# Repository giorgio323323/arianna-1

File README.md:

# Arianna
Arianna: il robot biblitecario.

il progetto è stato portato in: https://github.com/giorgio323323/ARI_V3

## Introduzione

Da [Arianna by CSBNO](http://webopac.csbno.net/library/Canegrate/makers-lab/arianna/) :
> Arrivo in biblioteca e chiedo “Robinia Blues” di Valter Binaghi, il bibliotecario consulta il computer e mi informa che c’è e lo posso trovare tra gli autori italiani. Un attimo di imbarazzo, non frequento questo luogo abbastanza da conoscere la disposizione degli scaffali, faccio per domandare ma il mio interlocutore mi anticipa dicendomi di seguire Arianna. Arianna? Un sibilo mi fa voltare, vedo una macchinina che parte lungo il corridoio, porta la scritta Arianna. Al mio sguardo interrogativo il mio interlocutore mi fa cenno di andare, segua Arianna mi dice. Tutto dura pochi secondi nei quali valuto anche la possibilità di essere vittima di “Scherzi a parte”, Arianna si ferma, si gira un poco e con un altro fruscio un puntatore luminoso si muove, si accende e quando decido di guardare dove Arianna sembra “indicare” vedo una luce sui libri e li vicino il mio “Robina Blues”. Lo prendo, lo sfoglio e me ne vado un poco stupito, saluto il bibliotecario e nel frattempo risento il sibilo. Vedo Arianna che torna da dove era venuta, la vedo accoccolarsi in una piccola casetta e io lascio la biblioteca pronto a rileggere il libro di un bravo insegnante che ha attraversato i nostri luoghi.

## Obiettivo 
La costruzione di un robot ***autonomo*** ed ***indipendente*** con lo scopo di accompagnare una persona al libro richiesto. La navigazione avviene in un ambiente dinamico dove anche i singli scaffali possono cambiare di posizione.

## Roadmap

- [x] Start
- [x] Primi prototipi (Ambros,Arianna,4rianna,..)
- Struttura
    - [ ] Arianna
    - [ ] Ambros
    - [ ] 4rianna
    - [ ] ..
- Movimento
    - [ ] Motori DC
    - [x] Stepper
    - [ ] Altro
- Altro
- [ ] Interazione biblio DB

## Contatti
[STUFFcube](https://stuffcube.wordpress.com/)

## License

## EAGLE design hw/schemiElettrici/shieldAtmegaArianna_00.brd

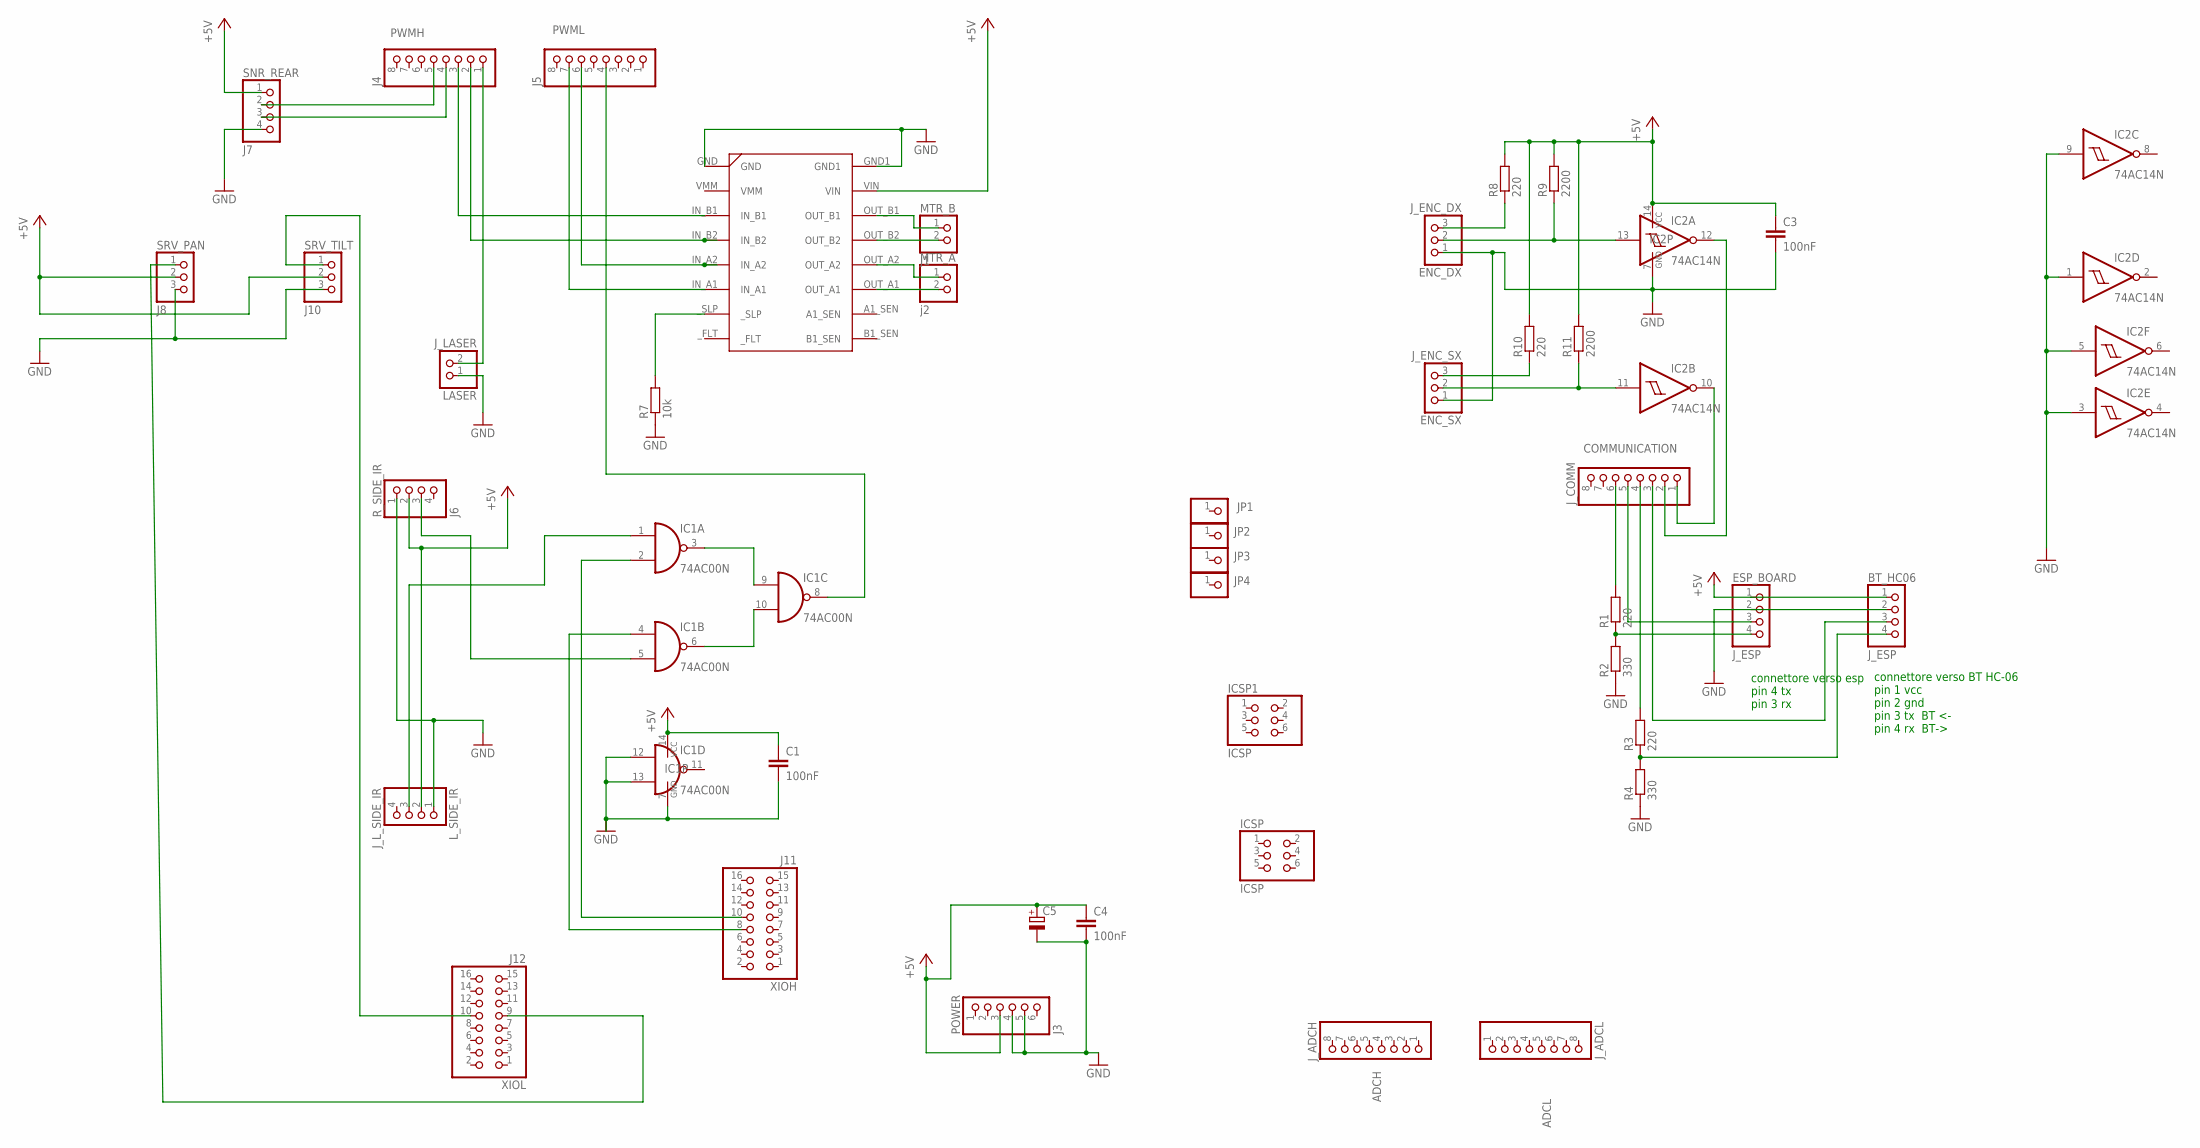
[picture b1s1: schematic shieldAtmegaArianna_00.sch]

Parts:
ADCH: J_ADCH; 1X08
ADCL: J_ADCL; 1X08
BT_HC06: J_ESP; 1X04
C1, C3, C4: 100nF; C050-025X075
C5: CPOL-EUE5-8.5; E5-8,5
COMMUNICATION: J_COMM; 1X08
ENC_DX: J_ENC_DX; 1X03
ENC_SX: J_ENC_SX; 1X03
ESP_BOARD: J_ESP; 1X04
IC1: 74AC00N; DIL14
IC2: 74AC14N; DIL14
ICSP, ICSP1: ICSP; 2X03
JP1, JP2, JP3, JP4: PINHD-1X1; 1X01
LASER: J_LASER; 1X02
L_SIDE_IR: J_L_SIDE_IR; 1X04
MTR_A: j2; 1X02
MTR_B: J1; 1X02
POWER: J3; 1X06
PWMH: J4; 1X08
PWML: J5; 1X08
R1, R3, R8, R10: 220; 0207/10
R2, R4: 330; 0207/10
R7: 10k; 0207/10
R9, R11: 2200; 0207/10
R_SIDE_IR: J6; 1X04
SNR_REAR: J7; 1X04
SRV_PAN: J8; 1X03
SRV_TILT: J10; 1X03
U$1: DRV8803; 8X5CARRIER
XIOH: J11; 2X08
XIOL: J12; 2X08

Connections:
+5V: BT_HC06.1, C1.1, C3.1, C4.1, C5.+, ESP_BOARD.1, IC1.14 (VCC), IC2.14 (VCC), L_SIDE_IR.2, POWER.3, R8.2, R9.2, R10.2, R11.2, R_SIDE_IR.2, SNR_REAR.1, SRV_PAN.2, SRV_TILT.2, U$1.VIN
ECHO: PWMH.4, SNR_REAR.3
GND: BT_HC06.2, C1.2, C3.2, C4.2, C5.-, ENC_DX.1, ENC_SX.1, ESP_BOARD.2, IC1.7 (GND), IC1.12 (I0), IC1.13 (I1), IC2.1 (I), IC2.3 (I), IC2.5 (I), IC2.7 (GND), IC2.9 (I), LASER.1, L_SIDE_IR.1, POWER.4, POWER.5, R2.1, R4.1, R7.1, R_SIDE_IR.1, SNR_REAR.4, SRV_PAN.3, SRV_TILT.3, U$1.GND, U$1.GND1
unnamed: MTR_B.1, U$1.OUT_B1
unnamed: MTR_B.2, U$1.OUT_B2
unnamed: MTR_A.1, U$1.OUT_A2
unnamed: SRV_TILT.1, XIOL.10
unnamed: SRV_PAN.1, XIOL.9
unnamed: MTR_A.2, U$1.OUT_A1
unnamed: PWML.7, U$1.IN_A1
unnamed: PWML.6, U$1.IN_A2
unnamed: PWMH.2, U$1.IN_B2
unnamed: PWMH.3, U$1.IN_B1
unnamed: ESP_BOARD.4, R1.1, R2.2
unnamed: BT_HC06.4, R3.1, R4.2
unnamed: COMMUNICATION.6, R1.2
unnamed: COMMUNICATION.4, R3.2
unnamed: COMMUNICATION.5, ESP_BOARD.3
unnamed: BT_HC06.3, COMMUNICATION.3
unnamed: IC1.3 (O), IC1.9 (I0)
unnamed: IC1.6 (O), IC1.10 (I1)
unnamed: LASER.2, PWMH.1
unnamed: IC1.2 (I1), XIOH.10
unnamed: IC1.5 (I1), R_SIDE_IR.3
unnamed: IC1.8 (O), PWML.4
unnamed: IC1.1 (I0), L_SIDE_IR.3
unnamed: IC1.4 (I0), XIOH.8
unnamed: R7.2, U$1._SLP
unnamed: ENC_DX.3, R8.1
unnamed: ENC_DX.2, IC2.13 (I), R9.1
unnamed: ENC_SX.3, R10.1
unnamed: PWMH.5, SNR_REAR.2
unnamed: ENC_SX.2, IC2.11 (I), R11.1
unnamed: COMMUNICATION.2, IC2.12 (O)
unnamed: COMMUNICATION.1, IC2.10 (O)

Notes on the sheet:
connettore verso esp pin 4 tx pin 3 rx
connettore verso BT HC-06 pin 1 vcc pin 2 gnd pin 3 tx BT <- pin 4 rx BT->

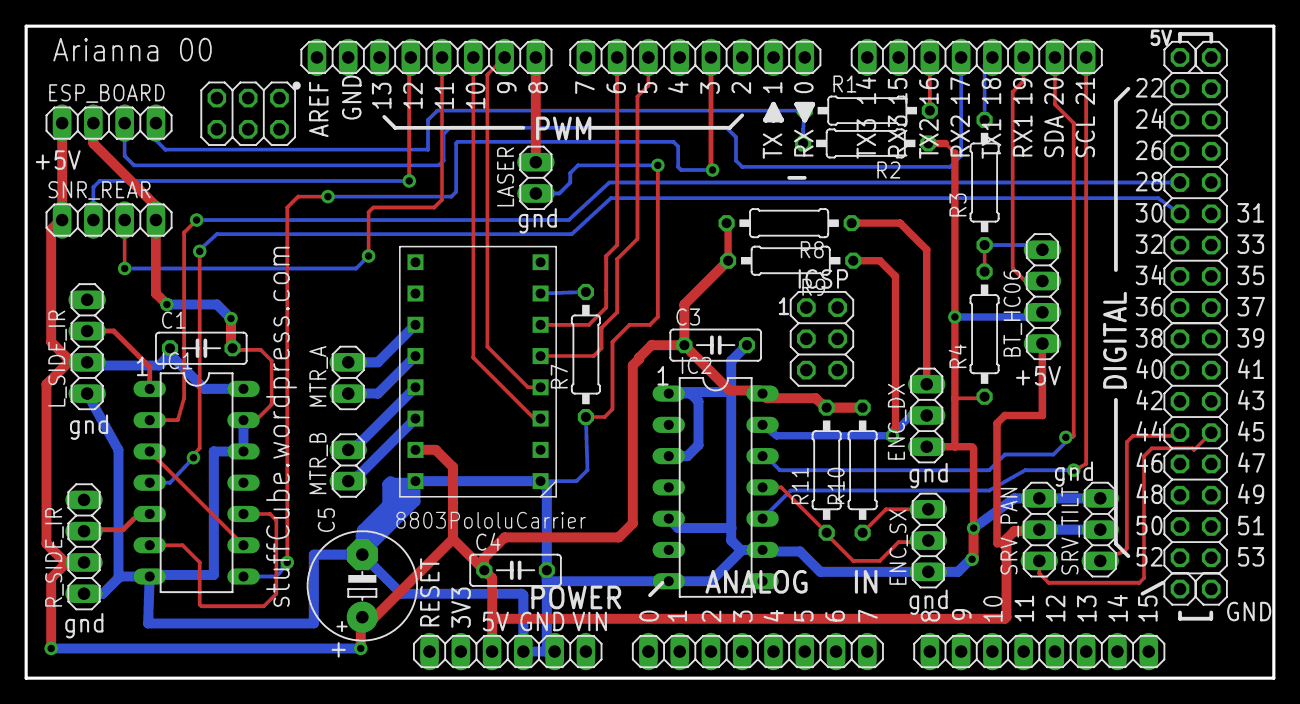
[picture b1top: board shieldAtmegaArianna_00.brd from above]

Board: 2 copper layers, 101.3 x 53.0 mm, 42 parts (0 on the bottom side), 35 nets.

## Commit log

2017-04-20 creazinoe folder, README e upload sketch per la gestione via seriale di 4rianna
2017-04-20 creazione folder, README e upload sketch per la gestione via seriale di 4rianna
2017-05-03 tentativo linee accelerate
2017-05-03 caricato file
2017-05-03 feed xy funziona correttamente, implementate funzioni G0 G1
2017-05-03 aggiunta risposta
2017-09-20 aggiornamento cartelle
2018-12-16 il progetto continua in un altro repository
2018-12-16 il progetto è stato portato in: https://github.com/giorgio323323/ARI_V3
